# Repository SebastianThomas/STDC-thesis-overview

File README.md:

# Linear-Exponential Algorithm-based Open Source Dive Computer

## Cloning this repository

To ensure all submodules are available locally, use the following command to 
check out the files: 

```bash
git clone --recurse-submodules git@git.ee.ethz.ch:pbl/FS2026/sebastian_thomas_653.git
```

## File Structure

```bash
.
├── 01_report
├── 02_presentation
├── KiCad
├── STDC_C
├── STDC-Ordering
├── STDC-Ordering.zip
├── STDC-STM32-rs
├── STDC-thalmann
└── README.md
```

## The `STDC-STM32-rs` project

This is the embedded firmware implementation, it is the module required to 
reproduce the experimental results, and to run the firmware on the PCB. 

### Setup environment

1. [Install Rust](https://rust-lang.org/tools/install/)
2. [Install just](https://just.systems/man/en/installation.html)
3. Add target for the embedded STM32 environment: `rustup target add thumbv7em-none-eabihf`

### Running code

It contains a `DEBUGGING.md` file with all the necessary information to debug
an application on the PCB and reproduce simulation results.

A `Justfile` is provided for convenience, it contains all required commands for
simulation, embedding, testing, CI, compiling and checking (without compiling).

It is recommended to use a STM32L476Rxx chip, as this is what the code is
tested on. Power it using a 3.7V fixed DC power supply. Attach the STLink V3
to the computer and debug JTAG pads exposed next to the MCU on the PCB, and 
run any `just` recipe that embeds software onto the MCU. After flashing, a 
terminal window will popup on top of the current session.

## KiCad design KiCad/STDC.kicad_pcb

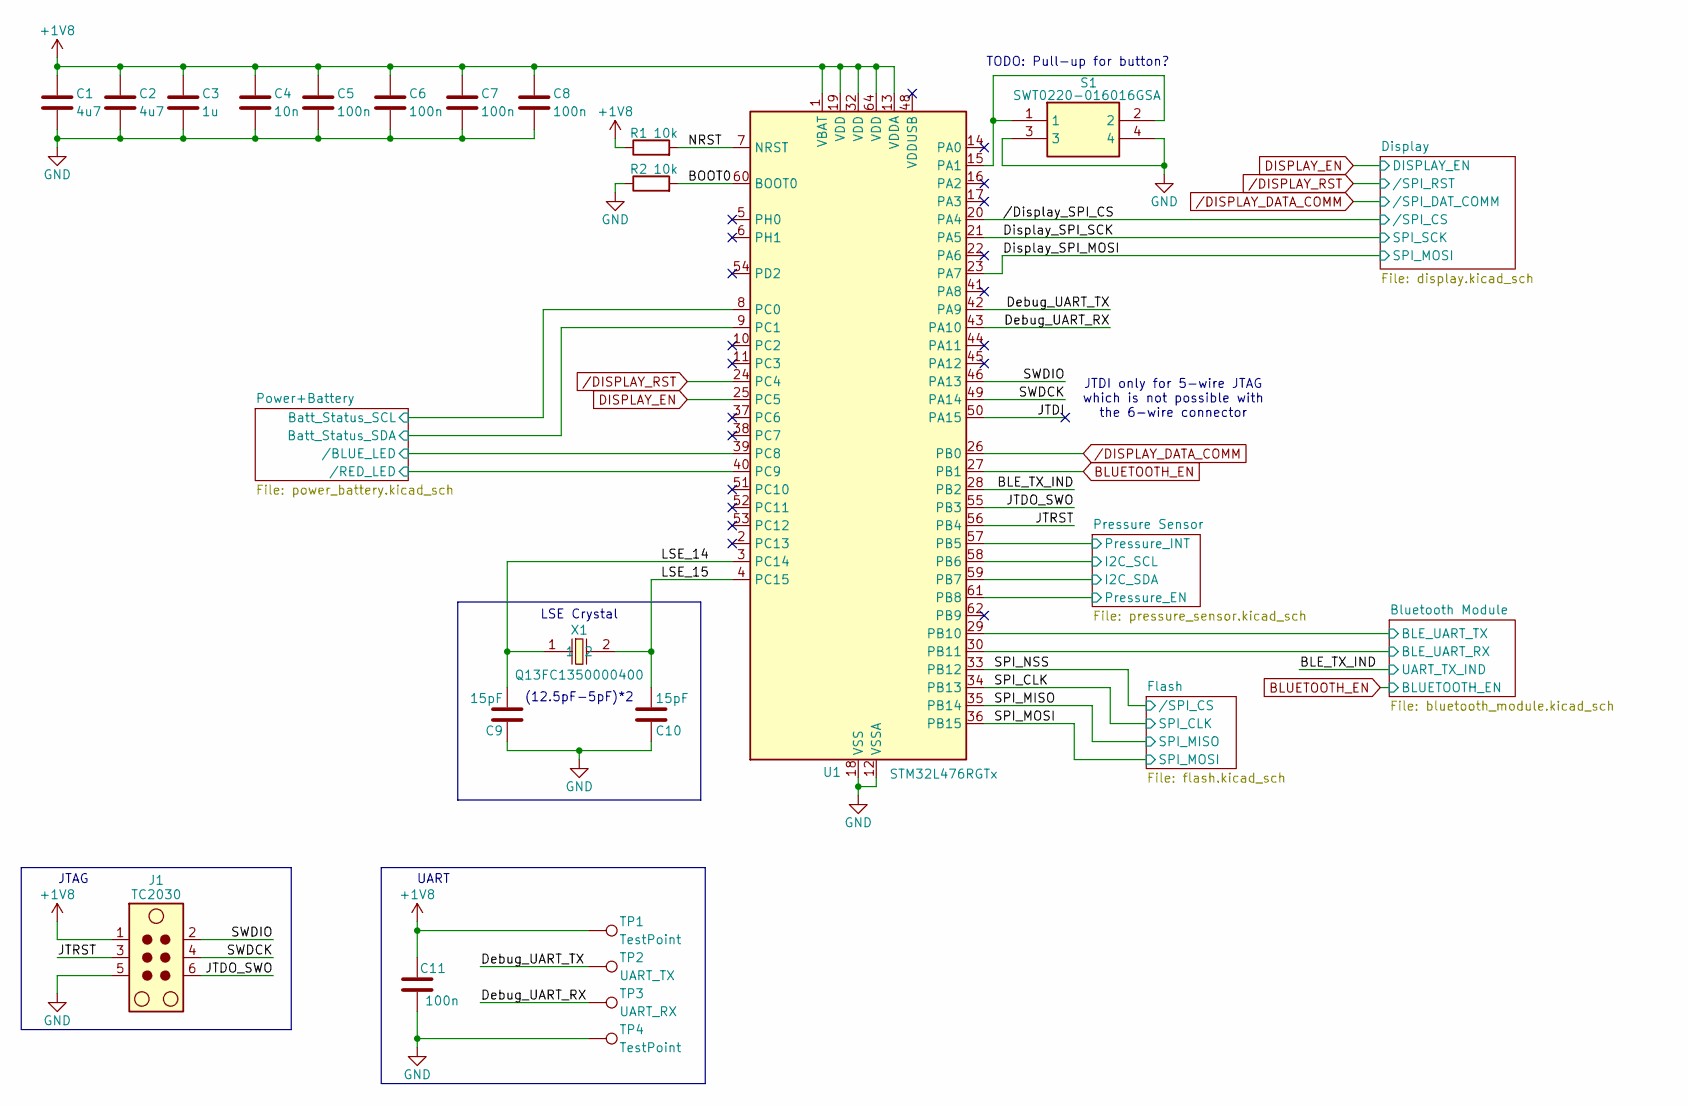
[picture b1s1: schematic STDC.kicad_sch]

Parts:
C1, C2: 4u7; C_0402_1005Metric
C3: 1u; C_0402_1005Metric
C4: 10n; C_0402_1005Metric
C5, C6, C7, C8, C11: 100n; C_0402_1005Metric
C9, C10: 15pF; C_0402_1005Metric
J1: TC2030; Tag-Connect_TC2030-IDC-NL_2x03_P1.27mm_Vertical
R1, R2: 10k; R_0402_1005Metric
S1: SWT0220-016016GSA; SWT0220016016GSA; Mouser Part Number 640-SWT0220016016GSA
TP1, TP4: TestPoint; TestPoint_THTPad_1.0x1.0mm_Drill0.5mm
TP2: UART_TX; TestPoint_THTPad_1.0x1.0mm_Drill0.5mm
TP3: UART_RX; TestPoint_THTPad_1.0x1.0mm_Drill0.5mm
U1: STM32L476RGTx; LQFP-64_10x10mm_P0.5mm
X1: Q13FC1350000400; Crystal_SMD_3215-2Pin_3.2x1.5mm; LCSC Part C32346

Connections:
+1V8: C1.1, C2.1, C3.1, C4.1, C5.1, C6.1, C7.1, C8.1, C11.1, J1.1, R1.1, TP1.1, U1.1 (VBAT), U1.13 (VDDA), U1.19 (VDD), U1.32 (VDD), U1.64 (VDD); also elsewhere on the board
/BLE_TX_IND: U1.28 (PB2); also elsewhere on the board
/BOOT0: R2.2, U1.60 (BOOT0)
/Bluetooth Module/BLE_UART_RX: U1.30 (PB11); also elsewhere on the board
/Bluetooth Module/BLE_UART_TX: U1.29 (PB10); also elsewhere on the board
/Debug_UART_RX: TP3.1, U1.43 (PA10)
/Debug_UART_TX: TP2.1, U1.42 (PA9)
/Display_SPI_MOSI: U1.23 (PA7); also elsewhere on the board
/Display_SPI_SCK: U1.21 (PA5); also elsewhere on the board
/JTDI: U1.50 (PA15)
/JTDO_SWO: J1.6, U1.55 (PB3)
/JTRST: J1.3, U1.56 (PB4)
/LSE_14: C9.2, U1.3 (PC14), X1.1
/LSE_15: C10.2, U1.4 (PC15), X1.2
/NRST: R1.2, U1.7 (NRST)
/Power+Battery/Batt_Status_SCL: U1.8 (PC0); also elsewhere on the board
/Power+Battery/Batt_Status_SDA: U1.9 (PC1); also elsewhere on the board
/Power+Battery//BLUE_LED: U1.39 (PC8); also elsewhere on the board
/Power+Battery//RED_LED: U1.40 (PC9); also elsewhere on the board
/Pressure Sensor/I2C_SCL: U1.58 (PB6); also elsewhere on the board
/Pressure Sensor/I2C_SDA: U1.59 (PB7); also elsewhere on the board
/Pressure Sensor/Pressure_EN: U1.61 (PB8); also elsewhere on the board
/Pressure Sensor/Pressure_INT: U1.57 (PB5); also elsewhere on the board
/SPI_CLK: U1.34 (PB13); also elsewhere on the board
/SPI_MISO: U1.35 (PB14); also elsewhere on the board
/SPI_MOSI: U1.36 (PB15); also elsewhere on the board
/SPI_NSS: U1.33 (PB12); also elsewhere on the board
/SWDCK: J1.4, U1.49 (PA14)
/SWDIO: J1.2, U1.46 (PA13)
//Display_SPI_CS: U1.20 (PA4); also elsewhere on the board
DISPLAY_EN: U1.25 (PC5); also elsewhere on the board
GND: C1.2, C2.2, C3.2, C4.2, C5.2, C6.2, C7.2, C8.2, C9.1, C10.1, C11.2, J1.5, R2.1, S1.3, S1.4, TP4.1, U1.12 (VSSA), U1.18 (VSS), U1.31 (VSS), U1.47 (VSS), U1.63 (VSS); also elsewhere on the board
unnamed: S1.1, S1.2, U1.15 (PA1)
/DISPLAY_DATA_COMM: U1.26 (PB0); also elsewhere on the board
/DISPLAY_RST: U1.24 (PC4); also elsewhere on the board

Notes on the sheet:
JTDI only for 5-wire JTAG which is not possible with the 6-wire connector
UART
TODO: Pull-up for button?
JTAG
(12.5pF-5pF)*2
LSE Crystal

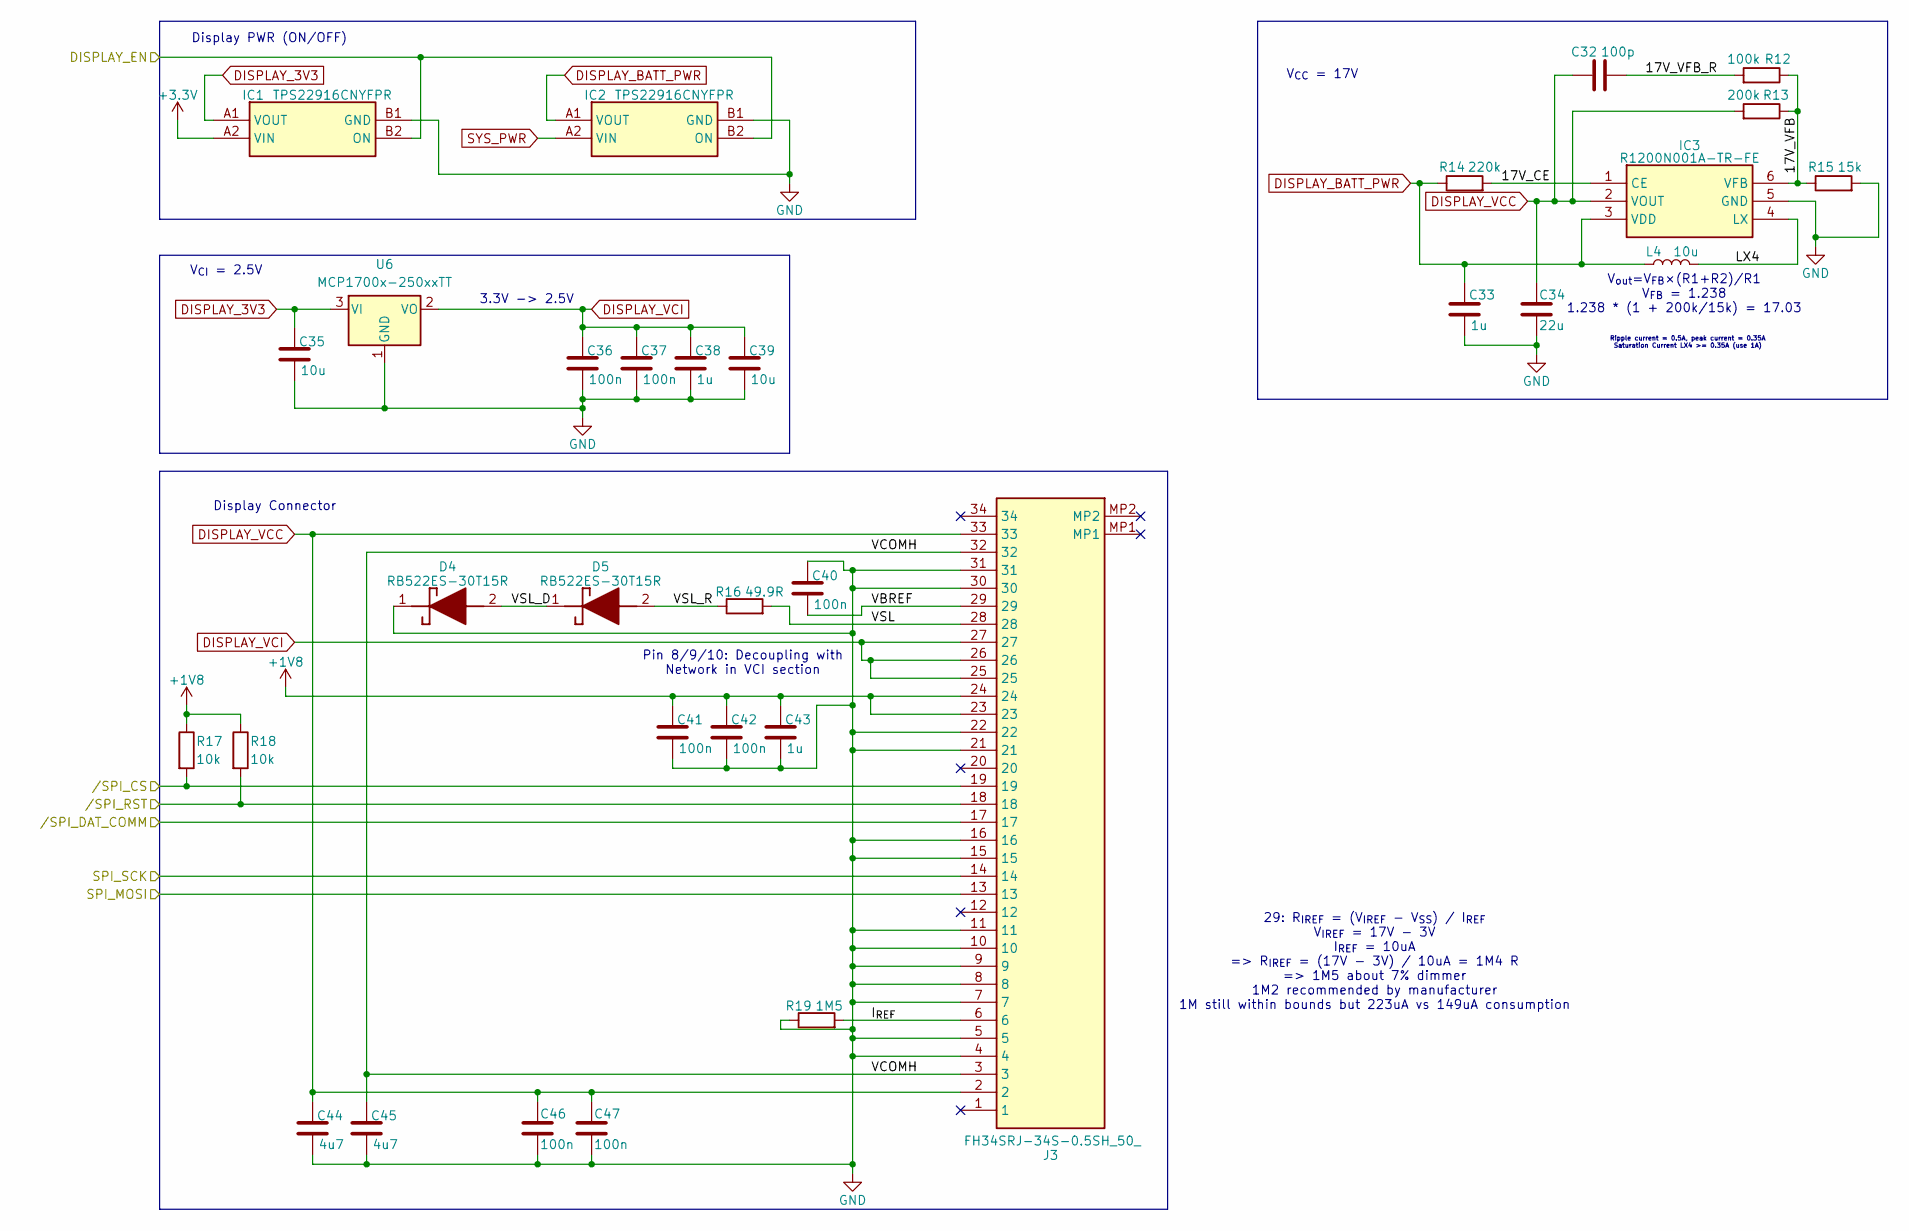
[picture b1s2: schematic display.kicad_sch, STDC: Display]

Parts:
C32: 100p; C_0402_1005Metric
C33, C38, C43: 1u; C_0402_1005Metric
C34: 22u; C_0402_1005Metric
C35, C39: 10u; C_0402_1005Metric
C36, C37, C40, C41, C42, C46, C47: 100n; C_0402_1005Metric
C44, C45: 4u7; C_0402_1005Metric
D4, D5: RB522ES-30T15R; RB522ES30; Mouser Part Number 755-RB522ES-30T15R
IC1, IC2: TPS22916CNYFPR; BGA4C40P2X2_78X78X50; Mouser Part Number 595-TPS22916CNYFPR
IC3: R1200N001A-TR-FE; SOT95P280X110-6N; Manufacturer_Part_Number R1200N001A-TR-FE
J3: FH34SRJ-34S-0.5SH_50_; FH34SRJ34S05SH50; Mouser Part Number 798-FH34SRJ34S05SH50
L4: 10u; L_1812_4532Metric
R12: 100k; R_0402_1005Metric
R13: 200k; R_0402_1005Metric
R14: 220k; R_0402_1005Metric
R15: 15k; R_0402_1005Metric
R16: 49.9R; R_0402_1005Metric
R17, R18: 10k; R_0402_1005Metric
R19: 1M5; R_0402_1005Metric
U6: MCP1700x-250xxTT; SOT-23

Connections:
+1V8: C41.1, C42.1, C43.1, J3.23, J3.24, R17.1, R18.1; also elsewhere on the board
/Display/17V_CE: IC3.1 (CE), R14.2
/Display/17V_VFB: IC3.6 (VFB), R12.1, R13.1, R15.1
/Display/17V_VFB_R: C32.2, R12.2
/Display/I_{REF}: J3.6, R19.2
/Display/LX4: IC3.4 (LX), L4.2
/Display/VBREF: C40.2, J3.29
/Display/VCOMH: C45.1, J3.3, J3.32
/Display/VSL: J3.28, R16.2
/Display/VSL_D: D4.2 (A), D5.1 (K)
/Display/VSL_R: D5.2 (A), R16.1
/Display_SPI_MOSI: J3.13; also elsewhere on the board
/Display_SPI_SCK: J3.14; also elsewhere on the board
//Display_SPI_CS: J3.19, R17.2; also elsewhere on the board
DISPLAY_3V3: C35.1, IC1.A1 (VOUT), U6.3 (VI)
DISPLAY_BATT_PWR: C33.1, IC2.A1 (VOUT), IC3.3 (VDD), L4.1, R14.1
DISPLAY_EN: IC1.B2 (ON), IC2.B2 (ON); also elsewhere on the board
DISPLAY_VCC: C32.1, C34.1, C44.1, C46.1, C47.1, IC3.2 (VOUT), J3.2, J3.33, R13.2
DISPLAY_VCI: C36.1, C37.1, C38.1, C39.1, J3.25, J3.26, J3.27, U6.2 (VO)
GND: C33.2, C34.2, C35.2, C36.2, C37.2, C38.2, C39.2, C40.1, C41.2, C42.2, C43.2, C44.2, C45.2, C46.2, C47.2, D4.1 (K), IC1.B1 (GND), IC2.B1 (GND), IC3.5 (GND), J3.4, J3.5, J3.7, J3.8, J3.9, J3.10, J3.11, J3.15, J3.16, J3.21, J3.22, J3.30, J3.31, R15.2, R19.1, U6.1 (GND); also elsewhere on the board
SYS_PWR: IC2.A2 (VIN); also elsewhere on the board
/DISPLAY_DATA_COMM: J3.17; also elsewhere on the board
/DISPLAY_RST: J3.18, R18.2; also elsewhere on the board

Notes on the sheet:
Ripple current = 0.5A, peak current = 0.35A Saturation Current LX4 >= 0.35A (use 1A)
Display PWR (ON/OFF)
V_{out}=V_{FB}×(R1+R2)/R1 V_{FB} = 1.238 1.238 * (1 + 200k/15k) = 17.03
Pin 8/9/10: Decoupling with Network in VCI section
3.3V -> 2.5V
Display Connector
29: R_{IREF} = (V_{IREF} - V_{SS}) / I_{REF} V_{IREF} = 17V - 3V I_{REF} = 10uA => R_{IREF} = (17V - 3V) / 10uA = 1M4 R => 1M5 about 7% dimmer 1M2 recommended by manufacturer 1M still within bounds but 223uA vs 149uA consumption
V_{CC} = 17V
V_{CI} = 2.5V

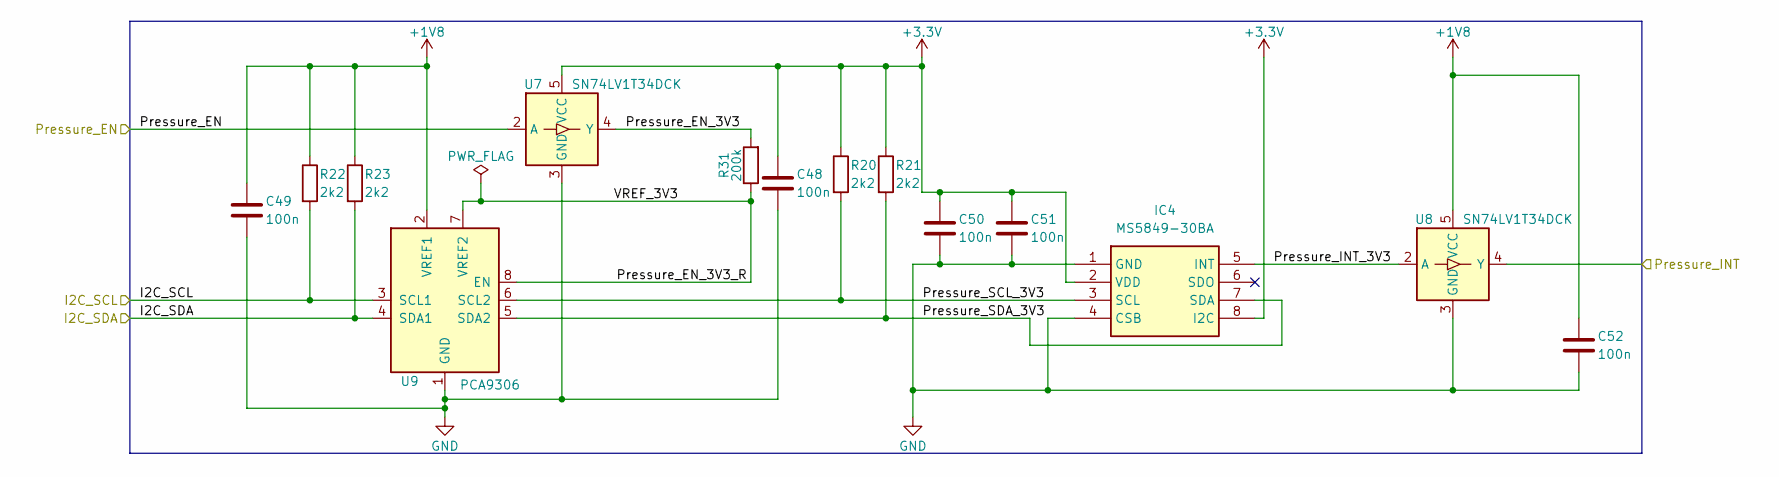
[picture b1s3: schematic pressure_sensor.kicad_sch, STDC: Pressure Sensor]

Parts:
C48, C49, C50, C51, C52: 100n; C_0402_1005Metric
IC4: MS5849-30BA; MS584930BA; Mouser Part Number 824-MS5849-30BA
R20, R21, R22, R23: 2k2; R_0402_1005Metric
R31: 200k; R_0402_1005Metric
U7, U8: SN74LV1T34DCK; SOT-353_SC-70-5
U9: PCA9306; X2SON-8_1.4x1mm_P0.35mm

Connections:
+1V8: C49.1, C52.1, R22.1, R23.1, U8.5 (VCC), U9.2 (VREF1); also elsewhere on the board
/Pressure Sensor/I2C_SCL: R22.2, U9.3 (SCL1); also elsewhere on the board
/Pressure Sensor/I2C_SDA: R23.2, U9.4 (SDA1); also elsewhere on the board
/Pressure Sensor/Pressure_EN: U7.2 (A); also elsewhere on the board
/Pressure Sensor/Pressure_INT: U8.4 (Y); also elsewhere on the board
/Pressure Sensor/Pressure_INT_3V3: IC4.5 (INT), U8.2 (A)
/Pressure Sensor/Pressure_SCL_3V3: IC4.3 (SCL), R20.2, U9.6 (SCL2)
/Pressure Sensor/Pressure_SDA_3V3: IC4.7 (SDA), R21.2, U9.5 (SDA2)
GND: C48.2, C49.2, C50.2, C51.2, C52.2, IC4.1 (GND), IC4.4 (CSB), U7.3 (GND), U8.3 (GND), U9.1 (GND); also elsewhere on the board

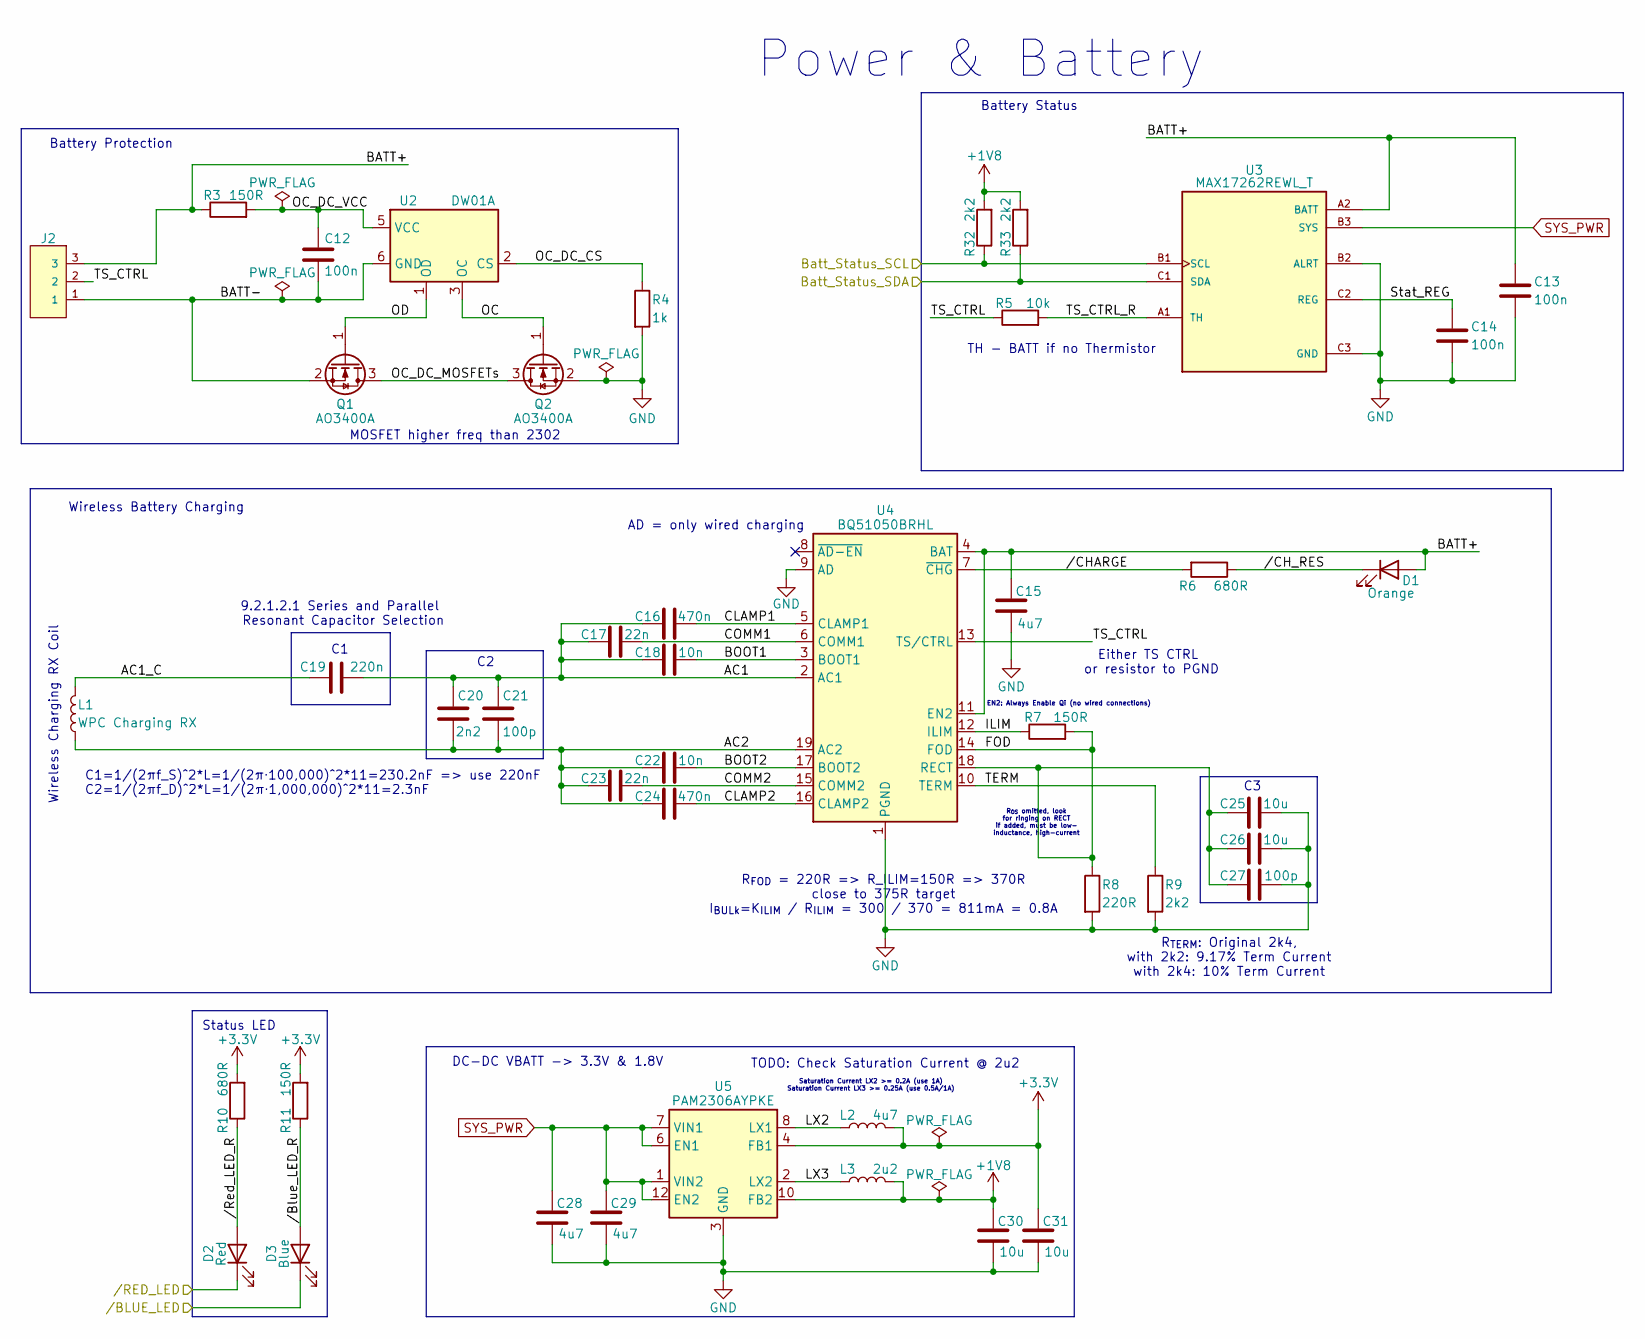
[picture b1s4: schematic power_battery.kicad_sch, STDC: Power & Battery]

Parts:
C12, C13, C14: 100n; C_0402_1005Metric
C15, C28, C29: 4u7; C_0402_1005Metric
C16, C24: 470n; C_0402_1005Metric
C17, C23: 22n; C_0402_1005Metric
C18, C22: 10n; C_0402_1005Metric
C19: 220n; C_0402_1005Metric
C20: 2n2; C_0402_1005Metric
C21, C27: 100p; C_0402_1005Metric
C25, C26, C30, C31: 10u; C_0402_1005Metric
D1: Orange; LED_0603_1608Metric
D2: Red; LED_0603_1608Metric
D3: Blue; LED_0603_1608Metric
J2: S3B-PH-SM4-TB_LF__SN_; JST_S3B-PH-SM4-TB_LF__SN_; PARTREV NA
L1: WPC Charging RX; L_IWAS4832ABEB110JF1
L2: 4u7; L_1210_3225Metric
L3: 2u2; L_1210_3225Metric
Q1, Q2: AO3400A; SOT-23
R3, R7, R11: 150R; R_0402_1005Metric
R4: 1k; R_0402_1005Metric
R5: 10k; R_0402_1005Metric
R6, R10: 680R; R_0402_1005Metric
R8: 220R; R_0402_1005Metric
R9, R32, R33: 2k2; R_0402_1005Metric
U2: DW01A; SOT-23-6
U3: MAX17262REWL_T; BGA9N40P3X3_144X146X69N
U4: BQ51050BRHL; Texas_VQFN-RHL-20
U5: PAM2306AYPKE; WDFN-12-1EP_3x3mm_P0.45mm_EP1.7x2.5mm

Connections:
+1V8: C30.1, L3.2, R32.2, R33.2, U5.10 (FB2); also elsewhere on the board
/Power+Battery/AC1: C16.1, C17.1, C18.1, C19.2, C20.1, C21.1, U4.2 (AC1)
/Power+Battery/AC1_C: C19.1, L1.2
/Power+Battery/AC2: C20.2, C21.2, C22.1, C23.1, C24.1, L1.1, U4.19 (AC2)
/Power+Battery/BATT+: C13.1, C15.1, D1.2 (A), J2.3, R3.1, U3.A2 (BATT), U4.4 (BAT), U4.11 (EN2)
/Power+Battery/BATT-: C12.2, J2.1, Q1.2 (S), U2.6 (GND)
/Power+Battery/BOOT1: C18.2, U4.3 (BOOT1)
/Power+Battery/BOOT2: C22.2, U4.17 (BOOT2)
/Power+Battery/Batt_Status_SCL: R32.1, U3.B1 (SCL); also elsewhere on the board
/Power+Battery/Batt_Status_SDA: R33.1, U3.C1 (SDA); also elsewhere on the board
/Power+Battery/CLAMP1: C16.2, U4.5 (CLAMP1)
/Power+Battery/CLAMP2: C24.2, U4.16 (CLAMP2)
/Power+Battery/COMM1: C17.2, U4.6 (COMM1)
/Power+Battery/COMM2: C23.2, U4.15 (COMM2)
/Power+Battery/FOD: C25.1, C26.1, C27.1, R7.2, R8.1, U4.14 (FOD), U4.18 (RECT)
/Power+Battery/ILIM: R7.1, U4.12 (ILIM)
/Power+Battery/LX2: L2.1, U5.8 (LX1)
/Power+Battery/LX3: L3.1, U5.2 (LX2)
/Power+Battery/OC: Q2.1 (G), U2.3 (OC)
/Power+Battery/OC_DC_CS: R4.1, U2.2 (CS)
/Power+Battery/OC_DC_MOSFETs: Q1.3 (D), Q2.3 (D)
/Power+Battery/OC_DC_VCC: C12.1, R3.2, U2.5 (VCC)
/Power+Battery/OD: Q1.1 (G), U2.1 (OD)
/Power+Battery/Stat_REG: C14.1, U3.C2 (REG)
/Power+Battery/TERM: R9.1, U4.10 (TERM)
/Power+Battery/TS_CTRL: J2.2, R5.1, U4.13 (TS/CTRL)
/Power+Battery/TS_CTRL_R: R5.2, U3.A1 (TH)
/Power+Battery//BLUE_LED: D3.1 (K); also elsewhere on the board
/Power+Battery//Blue_LED_R: D3.2 (A), R11.1
/Power+Battery//CHARGE: R6.2, U4.7 (~CHG)
/Power+Battery//CH_RES: D1.1 (K), R6.1
/Power+Battery//RED_LED: D2.1 (K); also elsewhere on the board
/Power+Battery//Red_LED_R: D2.2 (A), R10.1
GND: C13.2, C14.2, C15.2, C25.2, C26.2, C27.2, C28.2, C29.2, C30.2, C31.2, Q2.2 (S), R4.2, R8.2, R9.2, U3.B2 (ALRT), U3.C3 (GND), U4.1 (PGND), U4.9 (AD), U4.20 (PGND), U4.21 (PGND), U5.3 (GND), U5.9 (GND), U5.13 (GND); also elsewhere on the board
SYS_PWR: C28.1, C29.1, U3.B3 (SYS), U5.1 (VIN2), U5.6 (EN1), U5.7 (VIN1), U5.12 (EN2); also elsewhere on the board

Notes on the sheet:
Power & Battery
Wireless Battery Charging
DC-DC VBATT -> 3.3V & 1.8V
C2​=1/(2πf_D​)^2*L​=1/(2π⋅1,000,000)^2*11=2.3nF
R_{FOD} = 220R => R_ILIM=150R => 370R close to 375R target I_{BULk}=K_{ILIM} / R_{ILIM} = 300 / 370 = 811mA = 0.8A
Status LED
C1​=1/(2πf_S​)^2*L​=1/(2π⋅100,000)^2*11=230.2nF => use 220nF
Either TS CTRL or resistor to PGND
Wireless Charging RX Coil
MOSFET higher freq than 2302
R_{TERM}: Original 2k4, with 2k2: 9.17% Term Current with 2k4: 10% Term Current
Saturation Current LX2 >= 0.2A (use 1A) Saturation Current LX3 >= 0.25A (use 0.5A/1A)
9.2.1.2.1 Series and Parallel Resonant Capacitor Selection
TODO: Check Saturation Current @ 2u2
TH - BATT if no Thermistor
Battery Protection
AD = only wired charging
R_{OS} omitted, look for ringing on RECT if added, must be low- inductance, high-current
Battery Status
EN2: Always Enable Qi (no wired connections)

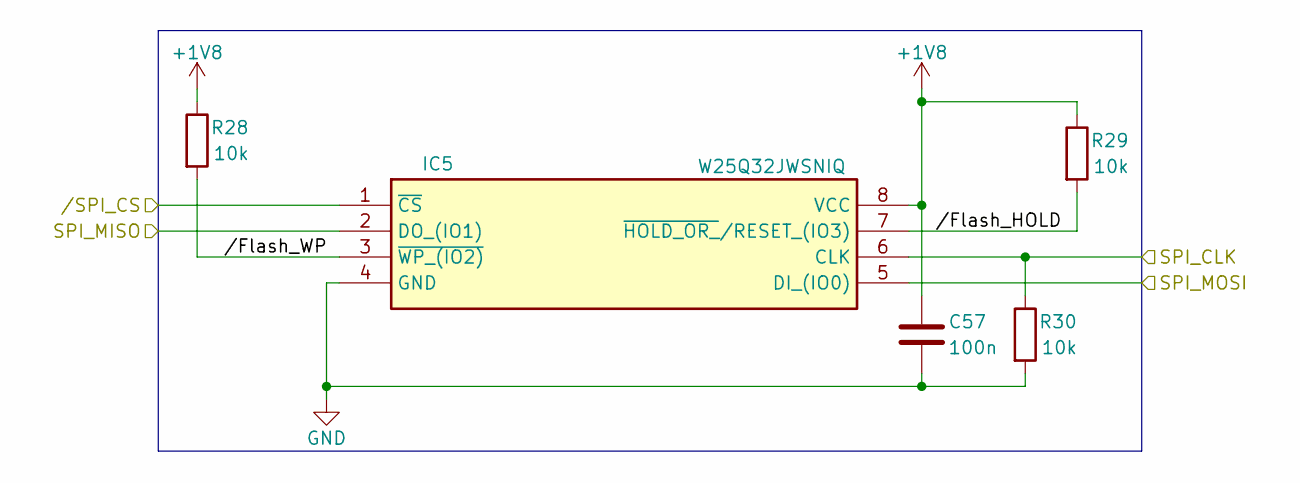
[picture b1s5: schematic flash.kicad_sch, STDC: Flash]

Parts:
C57: 100n; C_0402_1005Metric
IC5: W25Q32JWSNIQ; SOIC127P600X175-8N; Manufacturer_Part_Number W25Q32JWSNIQ; Mouser Part Number 454-W25Q32JWSNIQ
R28, R29, R30: 10k; R_0402_1005Metric

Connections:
+1V8: C57.1, IC5.8 (VCC), R28.1, R29.1; also elsewhere on the board
/Flash//Flash_HOLD: IC5.7 (~HOLD_OR_/RESET_(IO3)), R29.2
/Flash//Flash_WP: IC5.3 (~WP_(IO2)), R28.2
/SPI_CLK: IC5.6 (CLK), R30.1; also elsewhere on the board
/SPI_MISO: IC5.2 (DO_(IO1)); also elsewhere on the board
/SPI_MOSI: IC5.5 (DI_(IO0)); also elsewhere on the board
/SPI_NSS: IC5.1 (~CS); also elsewhere on the board
GND: C57.2, IC5.4 (GND), R30.2; also elsewhere on the board

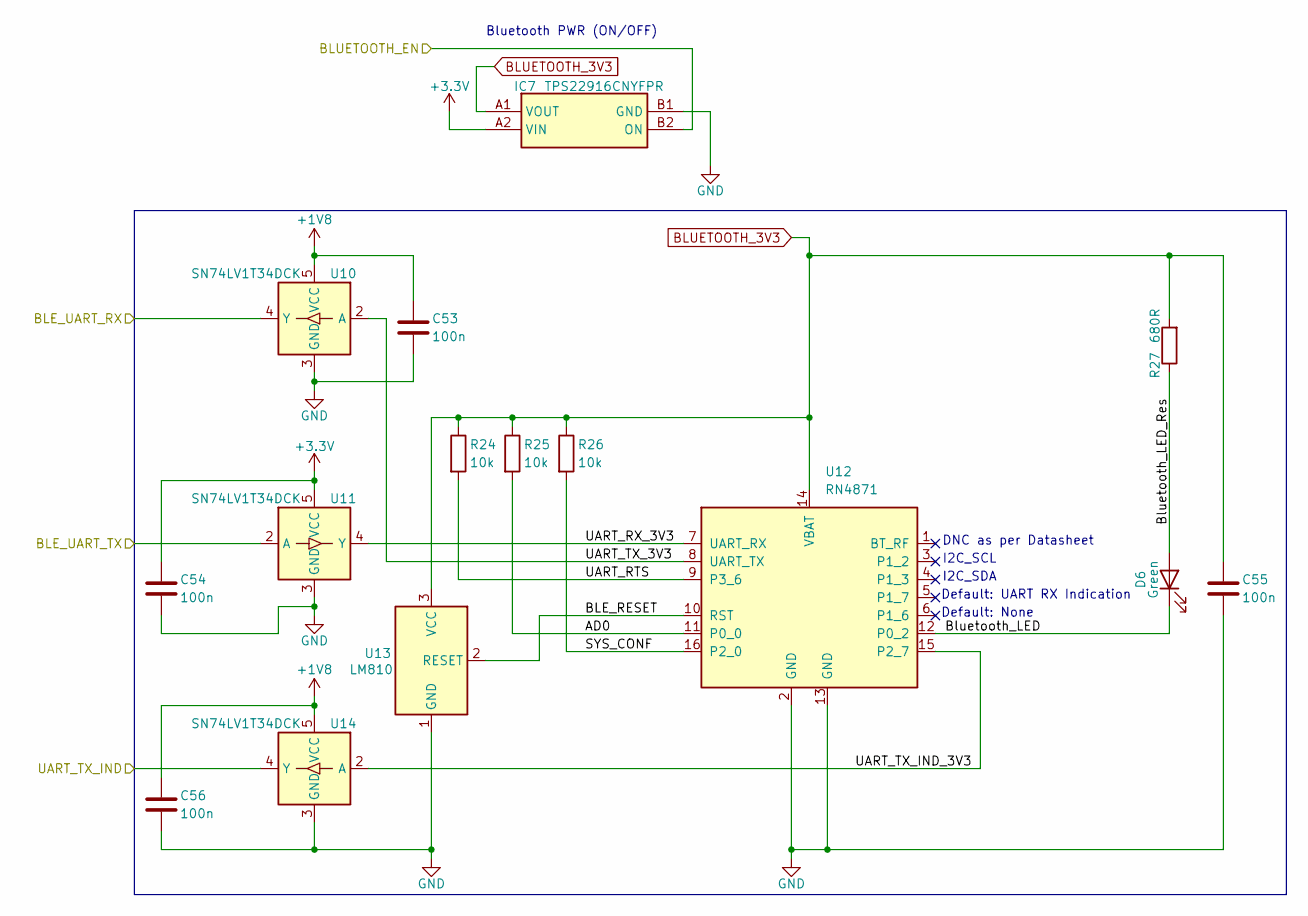
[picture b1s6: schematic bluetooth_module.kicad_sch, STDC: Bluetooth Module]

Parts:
C53, C54, C55, C56: 100n; C_0402_1005Metric
D6: Green; LED_0603_1608Metric
IC7: TPS22916CNYFPR; BGA4C40P2X2_78X78X50; Mouser Part Number 595-TPS22916CNYFPR
R24, R25, R26: 10k; R_0402_1005Metric
R27: 680R; R_0402_1005Metric
U10, U11, U14: SN74LV1T34DCK; SOT-353_SC-70-5
U12: RN4871; Microchip_RN4871
U13: LM810; SOT-23

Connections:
+1V8: C53.1, C56.1, U10.5 (VCC), U14.5 (VCC); also elsewhere on the board
/BLE_TX_IND: U14.4 (Y); also elsewhere on the board
/Bluetooth Module/AD0: R25.2, U12.11 (P0_0)
/Bluetooth Module/BLE_RESET: U12.10 (RST), U13.2 (RESET)
/Bluetooth Module/BLE_UART_RX: U10.4 (Y); also elsewhere on the board
/Bluetooth Module/BLE_UART_TX: U11.2 (A); also elsewhere on the board
/Bluetooth Module/Bluetooth_LED: D6.1 (K), U12.12 (P0_2)
/Bluetooth Module/Bluetooth_LED_Res: D6.2 (A), R27.1
/Bluetooth Module/SYS_CONF: R26.2, U12.16 (P2_0)
/Bluetooth Module/UART_RTS: R24.2, U12.9 (P3_6)
/Bluetooth Module/UART_RX_3V3: U11.4 (Y), U12.7 (UART_RX)
/Bluetooth Module/UART_TX_3V3: U10.2 (A), U12.8 (UART_TX)
/Bluetooth Module/UART_TX_IND_3V3: U12.15 (P2_7), U14.2 (A)
GND: C53.2, C54.2, C55.2, C56.2, IC7.B1 (GND), U10.3 (GND), U11.3 (GND), U12.2 (GND), U12.13 (GND), U13.1 (GND), U14.3 (GND); also elsewhere on the board

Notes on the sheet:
Default: UART RX Indication
DNC as per Datasheet
Default: None
I2C_SCL
Bluetooth PWR (ON/OFF)
I2C_SDA

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
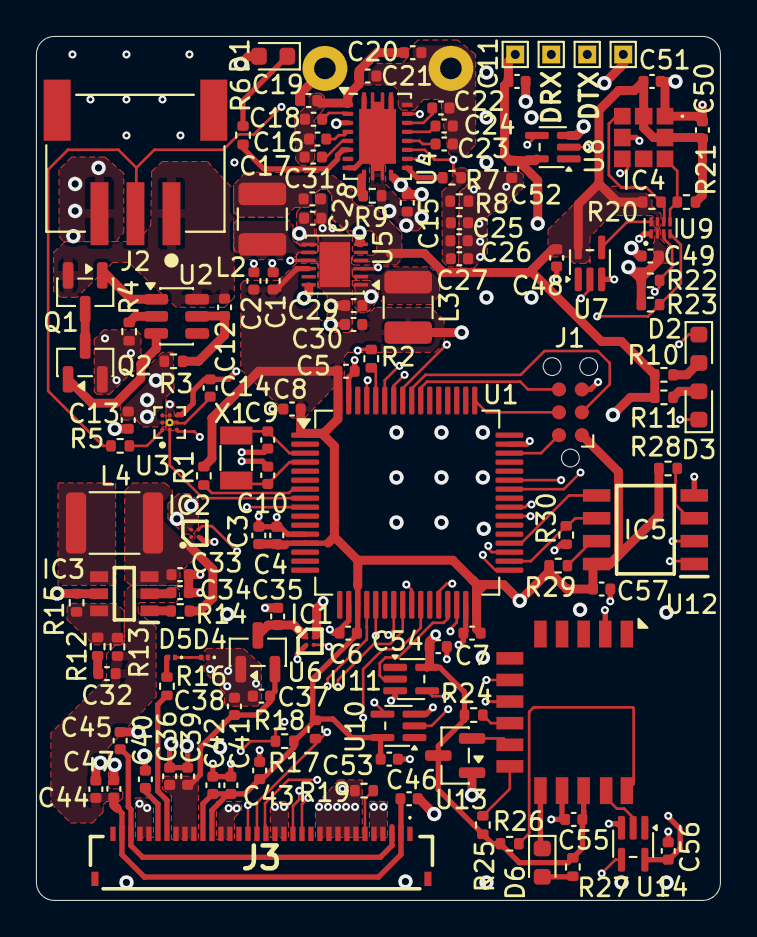
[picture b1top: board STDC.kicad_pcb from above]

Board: 4 copper layers, 38.0 x 48.0 mm, 126 parts (0 on the bottom side), 92 nets.

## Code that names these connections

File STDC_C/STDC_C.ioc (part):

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Mcu.Name=STM32L476R(C-E-G)Tx
Mcu.Package=LQFP64
Mcu.UserName=STM32L476RGTx
PA1.GPIOParameters=GPIO_PuPd,GPIO_Label,GPIO_ModeDefaultEXTI
PA1.GPIO_Label=Button
PA1.GPIO_ModeDefaultEXTI=GPIO_MODE_IT_FALLING
PA1.GPIO_PuPd=GPIO_PULLUP
PA1.Signal=GPXTI1
PA10.Mode=Asynchronous
PA10.Signal=USART1_RX
PA13\ (JTMS-SWDIO).Mode=JTAG_5_pins
PA13\ (JTMS-SWDIO).Signal=SYS_JTMS-SWDIO
PA14\ (JTCK-SWCLK).Mode=JTAG_5_pins
PA14\ (JTCK-SWCLK).Signal=SYS_JTCK-SWCLK
PA15\ (JTDI).Mode=JTAG_5_pins
PA15\ (JTDI).Signal=SYS_JTDI
PA4.GPIOParameters=GPIO_Label
PA4.GPIO_Label=_SPI1_CS
PA4.Signal=GPIO_Output
PA5.Mode=TX_Only_Simplex_Unidirect_Master
PA5.Signal=SPI1_SCK
PA7.Mode=TX_Only_Simplex_Unidirect_Master
PA7.Signal=SPI1_MOSI
PA9.Mode=Asynchronous
PA9.Signal=USART1_TX
PB0.GPIOParameters=GPIO_Label
PB0.GPIO_Label=_DISPLAY_DATA_COMM
PB0.Signal=GPIO_Output
PB1.GPIOParameters=GPIO_Label
PB1.GPIO_Label=Bluetooth_EN
PB1.Signal=GPIO_Output
PB10.Mode=Asynchronous
PB10.Signal=USART3_TX
PB11.Mode=Asynchronous
PB11.Signal=USART3_RX
PB12.Mode=NSS_Signal_Hard_Input
PB12.Signal=SPI2_NSS
PB13.Mode=Full_Duplex_Slave
PB13.Signal=SPI2_SCK
PB14.Mode=Full_Duplex_Slave
PB14.Signal=SPI2_MISO
PB15.Mode=Full_Duplex_Slave
PB15.Signal=SPI2_MOSI
PB2.GPIOParameters=GPIO_Label
PB2.GPIO_Label=UART_TX_IND
PB2.Signal=GPIO_Input
PB3\ (JTDO-TRACESWO).Mode=JTAG_5_pins
PB3\ (JTDO-TRACESWO).Signal=SYS_JTDO-SWO
PB4\ (NJTRST).Mode=JTAG_5_pins
PB4\ (NJTRST).Signal=SYS_JTRST
PB5.GPIOParameters=GPIO_Label
PB5.GPIO_Label=PRESSURE_INT
PB5.Signal=GPXTI5
PB6.Mode=I2C
PB6.Signal=I2C1_SCL
PB7.Mode=I2C
PB7.Signal=I2C1_SDA
PB8.GPIOParameters=GPIO_Label
PB8.GPIO_Label=PRESSURE_EN
PB8.Signal=GPIO_Output
PC0.Mode=I2C
PC0.Signal=I2C3_SCL
PC1.Mode=I2C
PC1.Signal=I2C3_SDA
PC14-OSC32_IN\ (PC14).Mode=LSE-External-Oscillator
PC14-OSC32_IN\ (PC14).Signal=RCC_OSC32_IN
PC15-OSC32_OUT\ (PC15).Mode=LSE-External-Oscillator
PC15-OSC32_OUT\ (PC15).Signal=RCC_OSC32_OUT
PC4.GPIOParameters=GPIO_Label
PC4.GPIO_Label=_SPI_RST
PC4.Signal=GPIO_Output
PC5.GPIOParameters=GPIO_Label
PC5.GPIO_Label=Display_EN
PC5.Signal=GPIO_Output
PC8.GPIOParameters=GPIO_Label
PC8.GPIO_Label=_Blue_LED
PC8.Signal=GPIO_Output
PC9.GPIOParameters=GPIO_Label
PC9.GPIO_Label=_Red_LED
PC9.Signal=GPIO_Output
RCC.HSE_VALUE=8000000
RCC.SYSCLKFreq_VALUE=4000000
RCC.SYSCLKSource=RCC_SYSCLKSOURCE_PLLCLK
board=custom

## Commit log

2026-03-04 readme
2026-03-04 Add Power Flag on GND
2026-03-04 KiCad Project: Draft 01
2026-03-04 Fix .gitignore
2026-03-05 Add TODO to discuss tomorrow
2026-03-05 Add decoupling for external connectors
2026-03-06 Added some TODOs, fixed some TODOs
2026-03-06 Fix JTAG connector
2026-03-08 Testing connectors, SPI2 pinout, reannotate
2026-03-08 Calculate saturation current for coils and add comments
2026-03-08 Add todos
2026-03-08 Add Pull-Down on SPI Flash Clk as per STM32 Bootloader datasheet Rev 70/page 49
2026-03-08 Fix display Rs to fix 17V reference and consolidate BOM
    And add more info to R_{IREF}
2026-03-09 Organize components in power and display, setup PCB
2026-03-09 Use JLCPCB setup ported from Altium
    https://gitlab.ethz.ch/villanif/altium_files/-/tree/master/example_design_rules
2026-03-10 First Draft PCB Layout
2026-03-12 Implement Comments, Working on PCB Layout
2026-03-14 PCB Layout V0.1 with errors
2026-03-14 Fix almost all issues
2026-03-14 Fix all except clearance violations
2026-03-14 Some track spacing
2026-03-14 Power Regulator Layout Adjustment
2026-03-14 A bit more space for the connector
2026-03-14 Reimport from schematic
2026-03-14 Fix GND vias
2026-03-14 Smaller pad
2026-03-14 More space for Connector
2026-03-15 Use SMD SM4 Connector for JST PH Battery
2026-03-15 Fix Schematic Symbol Footprint Filter from Library for Battery
2026-03-15 More space for power planes, traces
2026-03-15 Display VCC more space
2026-03-15 Wider power traces
2026-03-15 Move Logo
2026-03-15 Polarity Silkscreen
2026-03-15 Easier VIA placement
2026-03-16 Use SMT connector for Battery
2026-03-22 Fix polarity of Bluetooth Status LED
2026-03-22 Reduce Cuts in reference plane
2026-03-22 Fewer GND cuts, 1.8V Routing for Pressure INT
2026-04-07 Move Connector down, fix silkscreen clearance errors, Stitching Vias for GND
2026-04-07 Generate output files with 0 mask expansion
2026-04-08 Update Libs for connector etc
2026-04-11 Ordering V1
2026-06-02 Add STDC_C basic generated project
2026-06-02 Add STDC-STM32-rs submodule
2026-06-02 Add STDC-thalmann module
2026-06-02 Add Report submodule
2026-06-03 Update Git Modules
2026-06-03 Update submodules
2026-06-04 Add README
2026-06-04 Update Submodule
2026-06-05 Update Submodules: Hand-In
2026-06-05 Add report submodule to readme
2026-06-16 Add Presentation
2026-06-16 Add turned in Presentation PDF
2026-06-17 Update Presentation
2026-06-17 V2 beginning with buttons, resistor, ...
2026-06-17 Display inverted
2026-06-17 Remove KiCad and STDC-ORdering
2026-06-17 Add PCB Submodule
